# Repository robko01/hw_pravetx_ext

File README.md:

# hw_pravetx_ext

This repo is dedicated to hold Schematics and PCB design files for the Robko01 Pravetz extension board.

The board is designed in KiCAD.

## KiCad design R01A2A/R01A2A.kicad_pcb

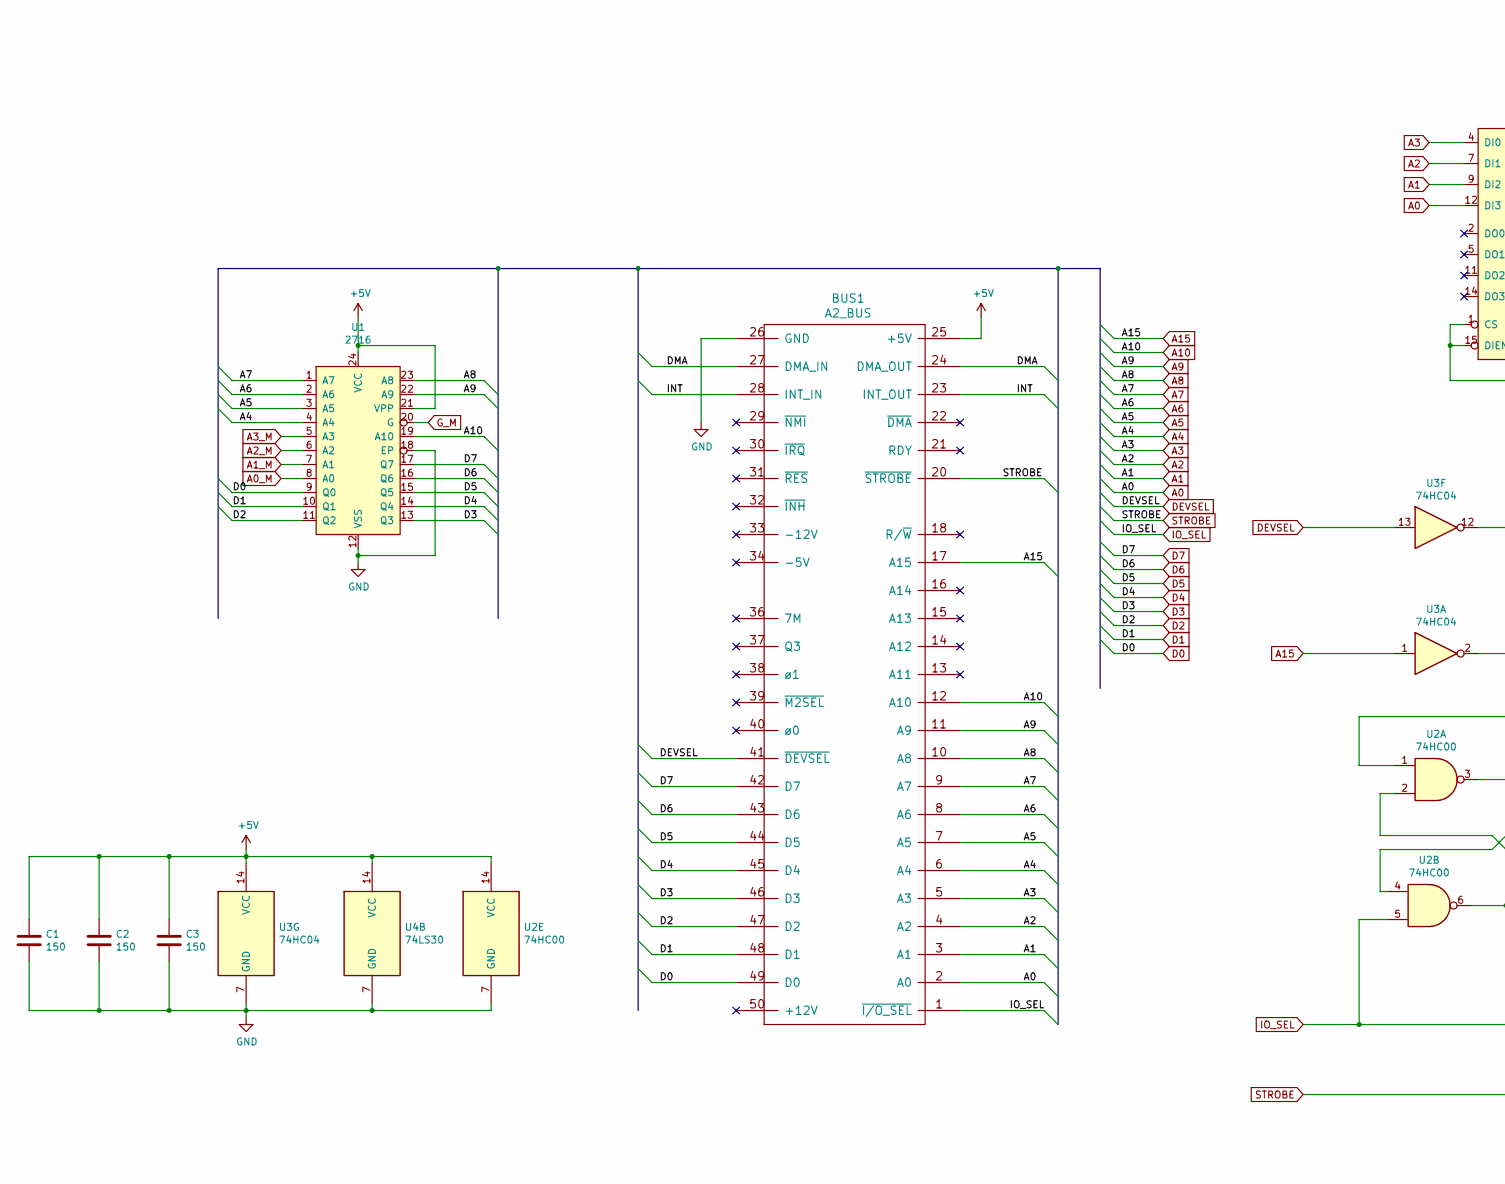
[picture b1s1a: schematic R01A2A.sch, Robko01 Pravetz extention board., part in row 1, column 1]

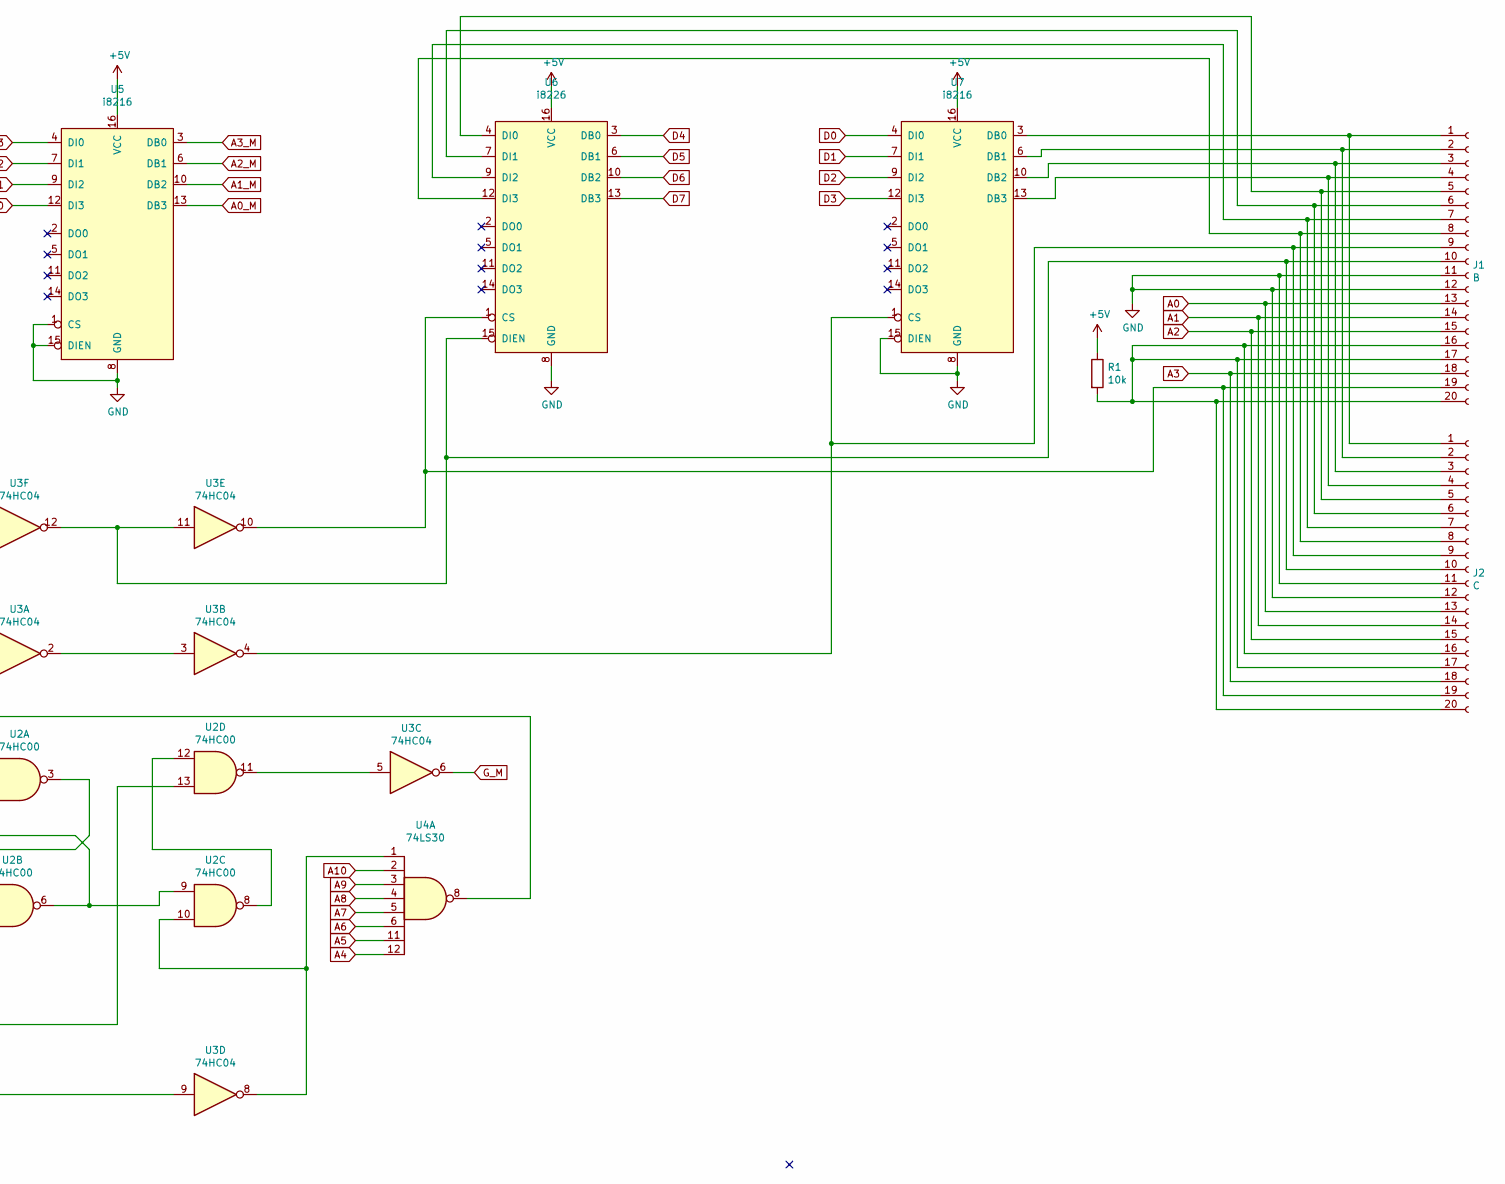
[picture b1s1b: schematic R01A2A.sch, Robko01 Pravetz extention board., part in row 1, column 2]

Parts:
BUS1: A2_BUS
C1, C2, C3: 150; C_Disc_D7.5mm_W2.5mm_P5.00mm
J1: B; R01A2A_Conn
J2: C; R01A2A_Conn
R1: 10k; R_Axial_DIN0207_L6.3mm_D2.5mm_P10.16mm_Horizontal
U1: 2716; DIP-24_W15.24mm
U2: 74HC00
U3: 74HC04
U4: 74LS30; DIP-14_W7.62mm
U5, U7: i8216; DIP-16_W7.62mm
U6: i8226; DIP-16_W7.62mm

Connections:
+5V: BUS1.25 (+5V), C1.1, C2.1, C3.1, R1.1, U1.21 (VPP), U1.24 (VCC), U2.14 (VCC), U3.14 (VCC), U4.14 (VCC), U5.16 (VCC), U6.16 (VCC), U7.16 (VCC)
/DMA: BUS1.24 (DMA_OUT), BUS1.27 (DMA_IN)
/INT: BUS1.23 (INT_OUT), BUS1.28 (INT_IN)
A0: BUS1.2 (A0), J1.13, J2.13, U5.12 (DI3)
A0_M: U1.8 (A0), U5.13 (DB3)
A1: BUS1.3 (A1), J1.14, J2.14, U5.9 (DI2)
A1_M: U1.7 (A1), U5.10 (DB2)
A2: BUS1.4 (A2), J1.15, J2.15, U5.7 (DI1)
A2_M: U1.6 (A2), U5.6 (DB1)
A3: BUS1.5 (A3), J1.18, J2.18, U5.4 (DI0)
A3_M: U1.5 (A3), U5.3 (DB0)
A4: BUS1.6 (A4), U1.4 (A4), U4.12
A5: BUS1.7 (A5), U1.3 (A5), U4.11
A6: BUS1.8 (A6), U1.2 (A6), U4.6
A7: BUS1.9 (A7), U1.1 (A7), U4.5
A8: BUS1.10 (A8), U1.23 (A8), U4.4
A9: BUS1.11 (A9), U1.22 (A9), U4.3
A10: BUS1.12 (A10), U1.19 (A10), U4.2
A15: BUS1.17 (A15), U3.1
D0: BUS1.49 (D0), U1.9 (Q0), U7.4 (DI0)
D1: BUS1.48 (D1), U1.10 (Q1), U7.7 (DI1)
D2: BUS1.47 (D2), U1.11 (Q2), U7.9 (DI2)
D3: BUS1.46 (D3), U1.13 (Q3), U7.12 (DI3)
D4: BUS1.45 (D4), U1.14 (Q4), U6.3 (DB0)
D5: BUS1.44 (D5), U1.15 (Q5), U6.6 (DB1)
D6: BUS1.43 (D6), U1.16 (Q6), U6.10 (DB2)
D7: BUS1.42 (D7), U1.17 (Q7), U6.13 (DB3)
DEVSEL: BUS1.41 (~DEVSEL), U3.13
GND: BUS1.26 (GND), C1.2, C2.2, C3.2, J1.11, J1.12, J2.11, J2.12, U1.12 (VSS), U1.18 (EP), U2.7 (GND), U3.7 (GND), U4.7 (GND), U5.1 (CS), U5.8 (GND), U5.15 (DIEN), U6.8 (GND), U7.8 (GND), U7.15 (DIEN)
G_M: U1.20 (G), U3.6
IO_SEL: BUS1.1 (~I/O_SEL), U2.5, U2.13
unnamed: J1.1, J2.1, U7.3 (DB0)
unnamed: J1.2, J2.2, U7.6 (DB1)
unnamed: J1.3, J2.3, U7.10 (DB2)
unnamed: J1.4, J2.4, U7.13 (DB3)
unnamed: J1.5, J2.5, U6.4 (DI0)
unnamed: J1.6, J2.6, U6.7 (DI1)
unnamed: J1.7, J2.7, U6.9 (DI2)
unnamed: J1.8, J2.8, U6.12 (DI3)
unnamed: J1.9, J2.9, U3.4, U7.1 (CS)
unnamed: J1.10, J2.10, U3.11, U3.12, U6.15 (DIEN)
unnamed: J1.16, J1.17, J1.20, J2.16, J2.17, J2.20, R1.2
unnamed: J1.19, J2.19, U3.10, U6.1 (CS)
unnamed: U2.1, U4.8
unnamed: U2.2, U2.6, U2.9
unnamed: U2.3, U2.4
unnamed: U2.10, U3.8, U4.1
unnamed: U2.11, U3.5
unnamed: U2.8, U2.12
unnamed: U3.2, U3.3
STROBE: BUS1.20 (~STROBE), U3.9

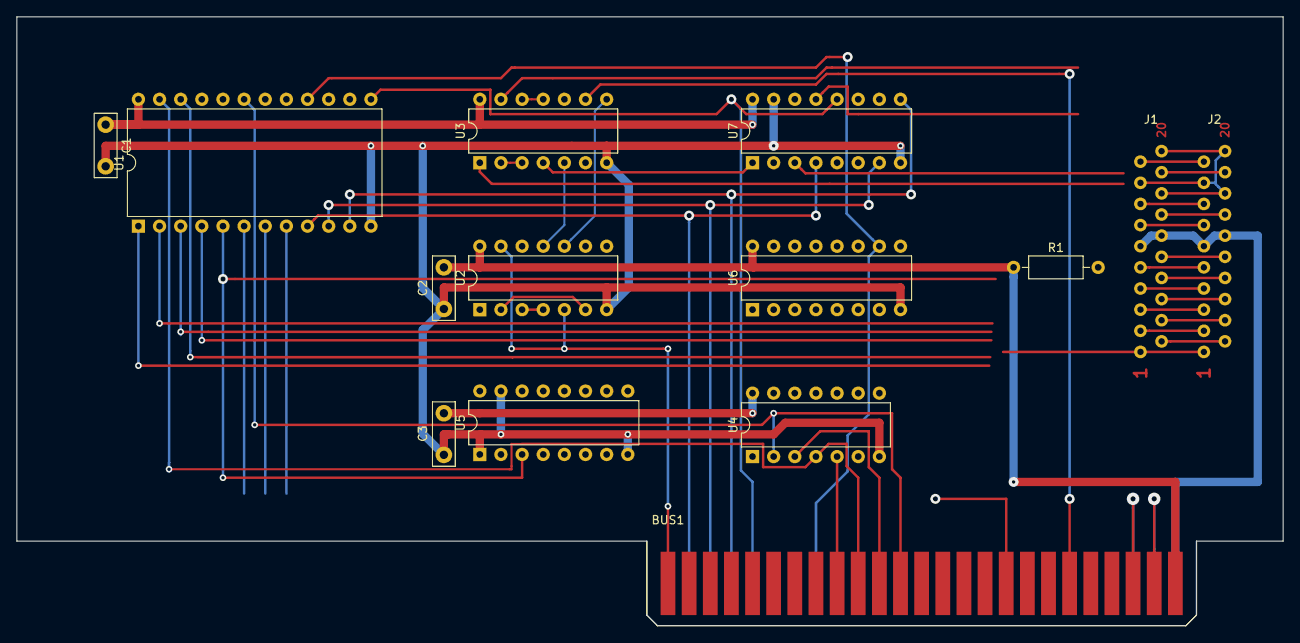
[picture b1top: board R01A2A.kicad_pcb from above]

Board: 2 copper layers, 152.1 x 73.2 mm, 14 parts (0 on the bottom side), 51 nets.

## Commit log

2020-08-17 Add design
2020-08-17 Change project libraries
2020-08-17 Remove one level of dir
2020-08-17 Fix in README
2020-08-17 Fix 2 in README
2020-08-30 Add ignore file
2020-08-30 Fix typo
